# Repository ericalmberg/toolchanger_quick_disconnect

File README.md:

# toolchanger_quick_disconnect

## Statement of Purpose

The PCB in here is intended to be a universal connector board based around the micro-molex 3.0 connectors commonly used in 3D printing electronics. This board in it's current iteration contains 4x 2-pin micro-molex connectors for connections to
- Heater catridge 
- Thermistor
- Part cooling fan
- Hotend fan

The board also includes on 4 pin XH2.54 connector for a stepper motor connection if the tool is direct drive, as well as pinout for 4 additional connections back to the duet for the user's purpose labeled accessory 1-4. These are provided in the form of 0.1" spaced through hole connections. 

The connection back to the duet is provided through a 2-row, 16 pin micro-molex 3.0 connector. The intention is that the toolchanger tool wiring could be replaced with one 16 pin connector, and tools could easily be interchanged to "live" and offline. This still requires a tool library to be built into the duet code in order to store tool pickup location offsets, configurations, z-offsets and any other parameters that need to be changed when switching between tools. 

## Potential Gotchas
 - Watch out for your thermistor/PT100 amplifier inputs. Since these are hardwired at the duet, on the same tool bay the user cannot swap between thermistor based tools and PT100/thermocouple based tools.

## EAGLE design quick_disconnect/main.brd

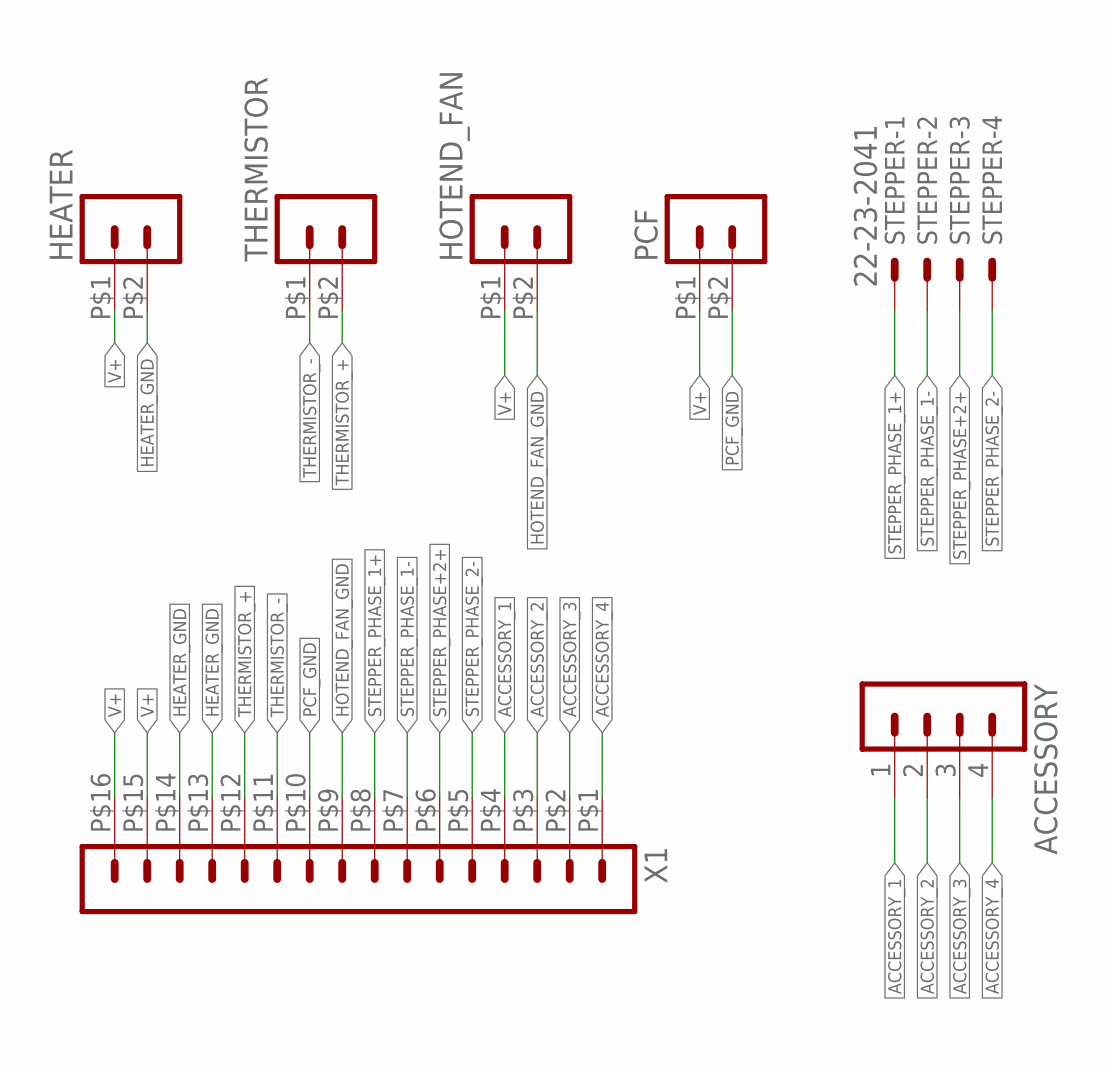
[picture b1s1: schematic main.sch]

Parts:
ACCESSORY: MA04-1
HEATER: HEADER_POS2_43650-0224; 43650-0224
HOTEND_FAN: HEADER_POS2_43650-0224; 43650-0224
PCF: HEADER_POS2_43650-0224; 43650-0224
STEPPER: 22-23-2041
THERMISTOR: HEADER_POS2_43650-0224; 43650-0224
X1: HEADER_POS16_43045-1618; 43045-1618

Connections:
ACCESSORY_1: ACCESSORY.1, X1.P$4 (4)
ACCESSORY_2: ACCESSORY.2, X1.P$3 (3)
ACCESSORY_3: ACCESSORY.3, X1.P$2 (2)
ACCESSORY_4: ACCESSORY.4, X1.P$1 (1)
HEATER_GND: HEATER.P$2 (2), X1.P$13 (13), X1.P$14 (14)
HOTEND_FAN_GND: HOTEND_FAN.P$2 (2), X1.P$9 (9)
PCF_GND: PCF.P$2 (2), X1.P$10 (10)
STEPPER_PHASE+2+: STEPPER.3, X1.P$6 (6)
STEPPER_PHASE_1+: STEPPER.1, X1.P$8 (8)
STEPPER_PHASE_1-: STEPPER.2, X1.P$7 (7)
STEPPER_PHASE_2-: STEPPER.4, X1.P$5 (5)
THERMISTOR_+: THERMISTOR.P$2 (2), X1.P$12 (12)
THERMISTOR_-: THERMISTOR.P$1 (1), X1.P$11 (11)
V+: HEATER.P$1 (1), HOTEND_FAN.P$1 (1), PCF.P$1 (1), X1.P$15 (15), X1.P$16 (16)

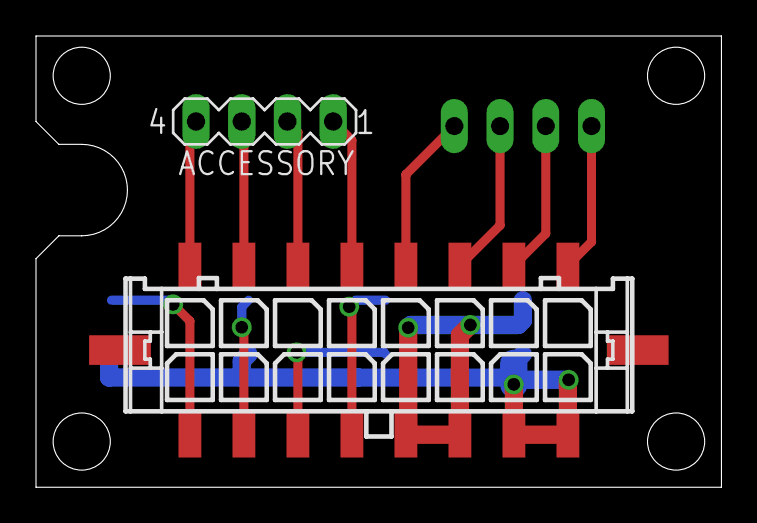
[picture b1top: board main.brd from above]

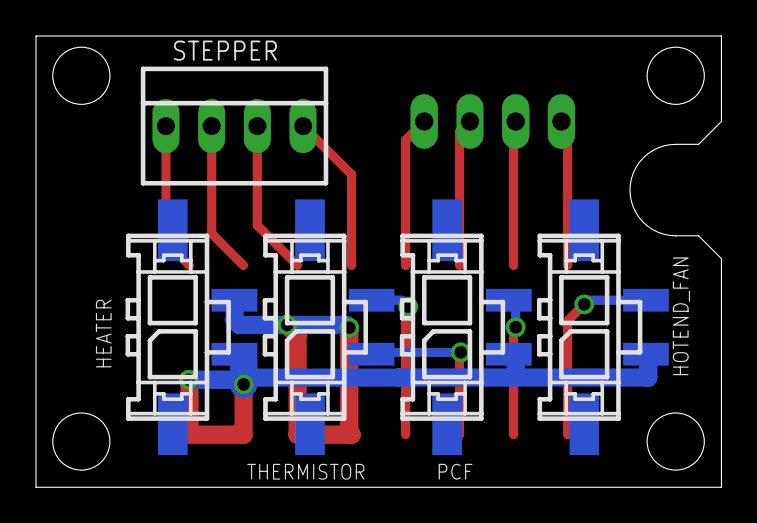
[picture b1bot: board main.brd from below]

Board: 2 copper layers, 38.1 x 25.1 mm, 7 parts (5 on the bottom side), 14 nets.

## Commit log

2019-10-23 first commit and schematic with only pogo pins
2020-01-22 initial design of 4x 2pin molex, 1x 16 pin molex, 4 header acc
2020-01-22 small routing updates
2020-01-22 Create LICENSE
    added GPL v3 open source license
2020-01-31 via updates to allow manual soldering, cutout on the side to allow for ptfe tube passthrough
